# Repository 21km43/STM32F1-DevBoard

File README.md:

# STM32F1 Development Board

## Summary
Schematic and Board layout of STM32F1 Development Board. This project was created using [KiCAD](https://www.kicad.org/).

## MCU
STM32F103C8T6  
72Mhz, 20KB RAM, 64KB ROM  
[Datasheet](https://www.st.com/resource/en/datasheet/stm32f103cb.pdf)

## Board order at JLCPCB
I recommend ordering this board from JLCPCB. This board uses only Basic or Preferred Extended Parts excluding USB connector. Therefore, if you order this board, the price will be relatively low. 

When order this board, pay attention to the following.
1. If it is a small volume production (qty <= 30 or 50) and the parts on the bottom side are not assembled, order this board with Economic PCBA.
2. Order number is specified under the USB Connector. So you should select "Specify a location" for "Remove Order Number" option. 
3. Tooling holes (Radius 1.152mm hole) is already installed. So you should select "Added by Customer" for "Tooling holes" option.
4. For orders over 30 or 50 pieces, import tax should be imposed customs duties. (The tax border changes depending on the type of import and exchange rate.)

Order cost is depends on part cost and so on. For reference, the following is a rough estimate of the price when ordering the quantity (include shipping cost) (When using the $9 SMT coupon distributed by JLCPCB every month).
*  2 qty -> $12 ($6/brd)
*  5 qty -> $19 ($3.8/brd)
* 30 qty -> $82 ($2.8/brd) <- Customs duties may be imposed

## Features
* STM32F103C8T6 ARM Cortex M3
* `72 MHz` maximum frequency, `64 KB` of Flash memory, `20 KB` of SRAM
* `8 MHz` crystal (High-Speed Enternal Clock)
* `32.768 KHz` crystal (Low-Speed External Clock)
* Green LED `PB2` Active high
* Red power LED `PWR`
* 2x20 side pins
* Size: `50.80 mm x 20.32 mm`

* SPI Flash (Optional)
  * PA4 CS
  * PA6 MISO
  * PA7 MOSI
  * PA5 SCK

* USB Type-C
  * PA11 USB_DN
  * PA12 USB_DP

### Supported FLASH
* [W25QJVSSIQ](https://www.digikey.jp/ja/products/detail/winbond-electronics/W25Q32JVSSIQ/5803981)
* [IS25LP040E](https://akizukidenshi.com/catalog/g/gI-18046/)

Most SPI FLASH should be available. Check FLASH pinout before assemble.

## Parts List
You can see parts list from the BOM below.  
[Parts List](/production/bom.csv)

## Board Image

## LICENSE
[MIT LICENSE](/LICENSE)  
You may use it freely for personal use, but if you wish to use it for commercial purposes, I would appreciate it if you could contact us.

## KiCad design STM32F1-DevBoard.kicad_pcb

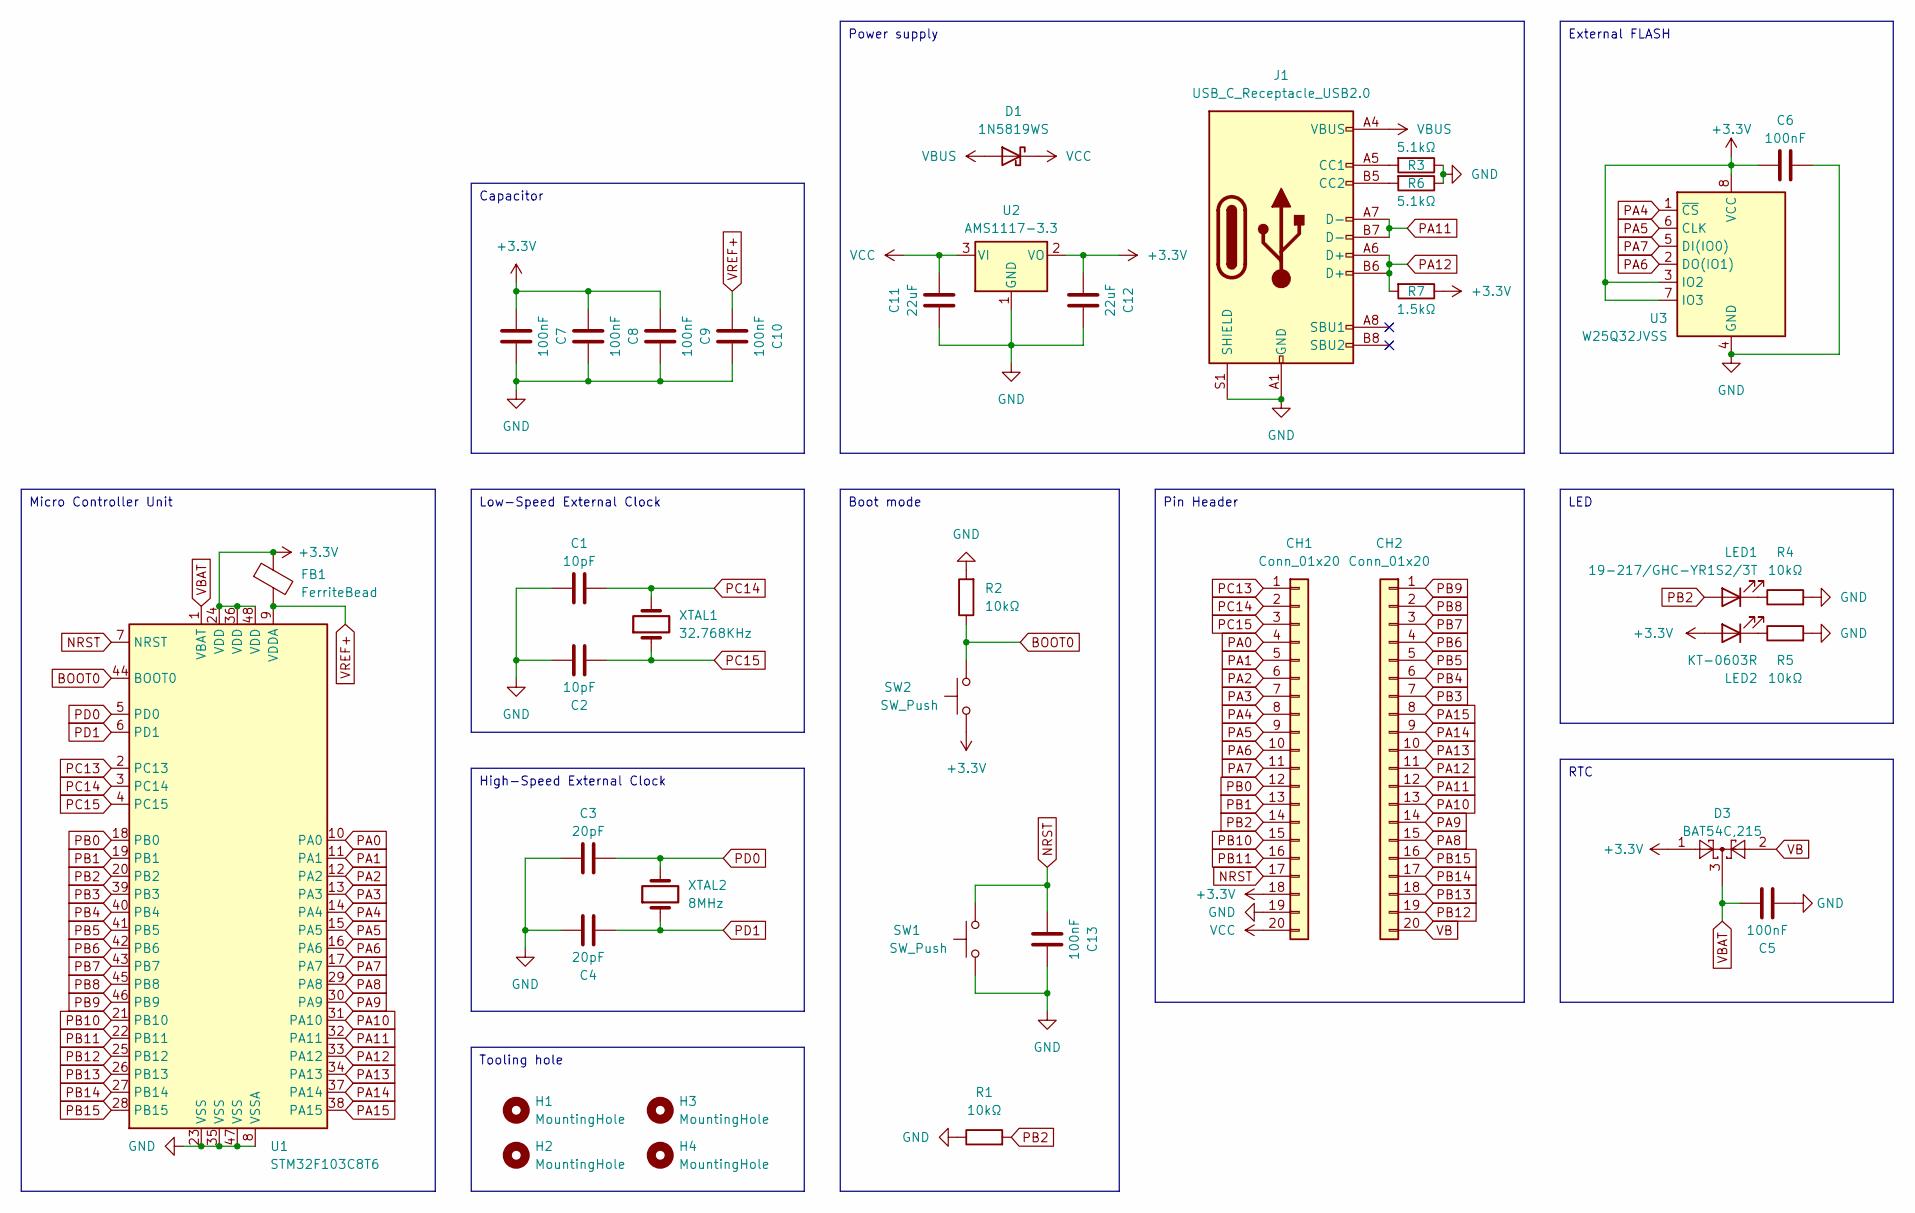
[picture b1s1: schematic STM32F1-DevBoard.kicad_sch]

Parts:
C1, C2: 10pF; C_0402_1005Metric; LCSC C32949
C3, C4: 20pF; C_0402_1005Metric; LCSC C1554
C5, C7, C8, C9, C10, C13: 100nF; C_0402_1005Metric; LCSC C1525
C6: 100nF; C_0603_1608Metric_Pad1.08x0.95mm_HandSolder; LCSC C14663
C11, C12: 22uF; C_0805_2012Metric; LCSC C45783
CH1, CH2: Conn_01x20; PinHeader_1x20_P2.54mm_Vertical
D1: 1N5819WS; D_SOD-323; LCSC C191023
D3: BAT54C,215; SOT-23; LCSC C37704
FB1: FerriteBead; L_0603_1608Metric; LCSC C1002
H1, H2, H3, H4: MountingHole; MountingHole_2.2mm_M2
J1: USB_C_Receptacle_USB2.0; USB_C_Receptacle_XKB_U262-16XN-4BVC11; LCSC C2765186
LED1: 19-217/GHC-YR1S2/3T; LED_0603_1608Metric; LCSC C72043
LED2: KT-0603R; LED_0603_1608Metric; LCSC C2286
R1, R2, R4, R5: 10kΩ; R_0402_1005Metric; LCSC C25744
R3, R6: 5.1kΩ; R_0402_1005Metric; LCSC C25905
R7: 1.5kΩ; R_0402_1005Metric; LCSC C25867
SW1, SW2: SW_Push; SW_SPST_TL3342; LCSC C318884
U1: STM32F103C8T6; LQFP-48_7x7mm_P0.5mm; LCSC C8734
U2: AMS1117-3.3; SOT-223-3_TabPin2; LCSC C6186
U3: W25Q32JVSS; SOIC-8_5.23x5.23mm_P1.27mm
XTAL1: 32.768KHz; Crystal_SMD_3215-2Pin_3.2x1.5mm; LCSC C32346
XTAL2: 8MHz; Crystal_SMD_5032-2Pin_5.0x3.2mm; LCSC C115962

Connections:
+3.3V: C6.1, C7.1, C8.1, C9.1, C12.1, CH1.18, D3.1, FB1.1, LED2.2 (A), R7.1, SW2.1, U1.24 (VDD), U1.36 (VDD), U1.48 (VDD), U2.2 (VO), U3.3 (IO2), U3.7 (IO3), U3.8 (VCC)
BOOT0: R2.1, SW2.2, U1.44 (BOOT0)
GND: C1.1, C2.2, C3.1, C4.2, C5.1, C6.2, C7.2, C8.2, C9.2, C10.2, C11.2, C12.2, C13.2, CH1.19, J1.A1 (GND), J1.A12 (GND), J1.B1 (GND), J1.B12 (GND), J1.S1 (SHIELD), R1.1, R2.2, R3.1, R4.2, R5.2, R6.1, SW1.1, U1.8 (VSSA), U1.23 (VSS), U1.35 (VSS), U1.47 (VSS), U2.1 (GND), U3.4 (GND)
NRST: C13.1, CH1.17, SW1.2, U1.7 (NRST)
unnamed: J1.A5 (CC1), R3.2
unnamed: J1.B5 (CC2), R6.2
unnamed: LED1.1 (K), R4.1
unnamed: LED2.1 (K), R5.1
PA0: CH1.4, U1.10 (PA0)
PA1: CH1.5, U1.11 (PA1)
PA2: CH1.6, U1.12 (PA2)
PA3: CH1.7, U1.13 (PA3)
PA4: CH1.8, U1.14 (PA4), U3.1 (~CS)
PA5: CH1.9, U1.15 (PA5), U3.6 (CLK)
PA6: CH1.10, U1.16 (PA6), U3.2 (DO(IO1))
PA7: CH1.11, U1.17 (PA7), U3.5 (DI(IO0))
PA8: CH2.15, U1.29 (PA8)
PA9: CH2.14, U1.30 (PA9)
PA10: CH2.13, U1.31 (PA10)
PA11: CH2.12, J1.A7 (D-), J1.B7 (D-), U1.32 (PA11)
PA12: CH2.11, J1.A6 (D+), J1.B6 (D+), R7.2, U1.33 (PA12)
PA13: CH2.10, U1.34 (PA13)
PA14: CH2.9, U1.37 (PA14)
PA15: CH2.8, U1.38 (PA15)
PB0: CH1.12, U1.18 (PB0)
PB1: CH1.13, U1.19 (PB1)
PB2: CH1.14, LED1.2 (A), R1.2, U1.20 (PB2)
PB3: CH2.7, U1.39 (PB3)
PB4: CH2.6, U1.40 (PB4)
PB5: CH2.5, U1.41 (PB5)
PB6: CH2.4, U1.42 (PB6)
PB7: CH2.3, U1.43 (PB7)
PB8: CH2.2, U1.45 (PB8)
PB9: CH2.1, U1.46 (PB9)
PB10: CH1.15, U1.21 (PB10)
PB11: CH1.16, U1.22 (PB11)
PB12: CH2.19, U1.25 (PB12)
PB13: CH2.18, U1.26 (PB13)
PB14: CH2.17, U1.27 (PB14)
PB15: CH2.16, U1.28 (PB15)
PC13: CH1.1, U1.2 (PC13)
PC14: C1.2, CH1.2, U1.3 (PC14), XTAL1.2
PC15: C2.1, CH1.3, U1.4 (PC15), XTAL1.1
PD0: C3.2, U1.5 (PD0), XTAL2.2
PD1: C4.1, U1.6 (PD1), XTAL2.1
VB: CH2.20, D3.2
VBAT: C5.2, D3.3, U1.1 (VBAT)
VBUS: D1.2 (A), J1.A4 (VBUS), J1.A9 (VBUS), J1.B4 (VBUS), J1.B9 (VBUS)
VCC: C11.1, CH1.20, D1.1 (K), U2.3 (VI)
VREF+: C10.1, FB1.2, U1.9 (VDDA)

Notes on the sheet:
External FLASH
Power supply
Pin Header
Tooling hole
RTC
High-Speed External Clock
Micro Controller Unit
Boot mode
LED
Capacitor
Low-Speed External Clock

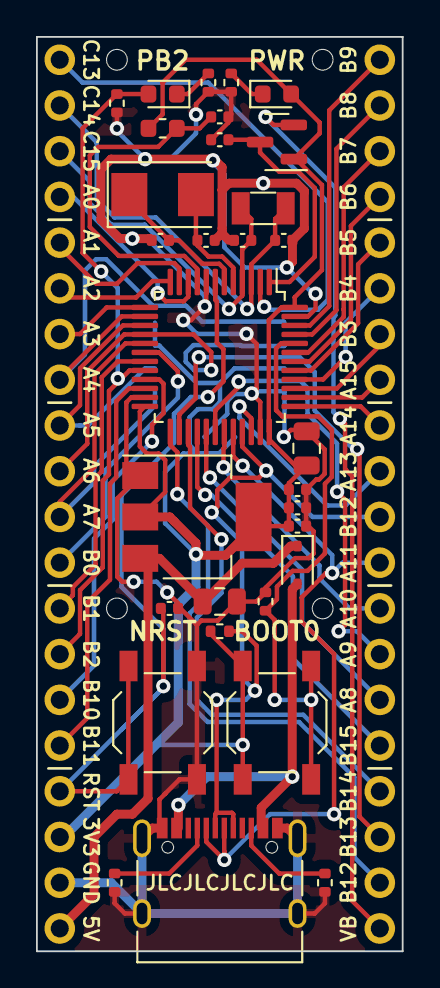
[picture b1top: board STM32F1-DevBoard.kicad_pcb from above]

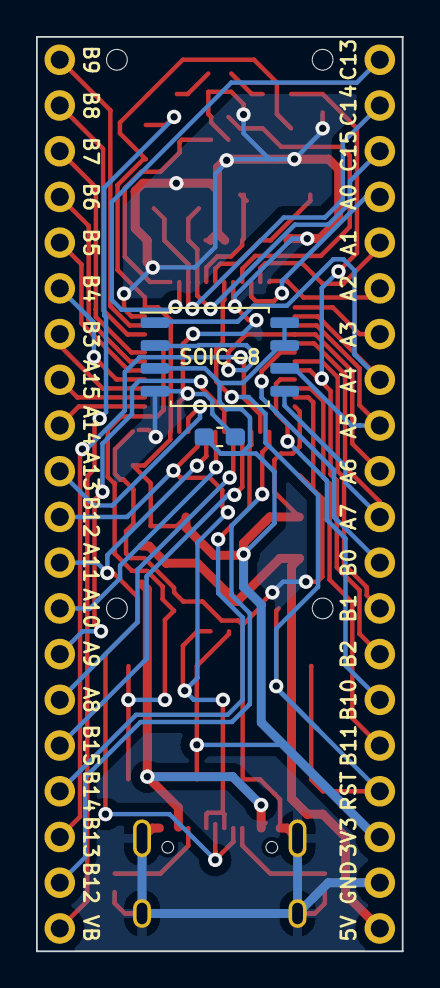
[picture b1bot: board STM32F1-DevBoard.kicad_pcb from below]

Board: 2 copper layers, 20.3 x 50.8 mm, 39 parts (4 on the bottom side), 50 nets.
